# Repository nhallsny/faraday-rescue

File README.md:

# faraday-rescue
Open source battery for e-bikes made by the now-defunct Faraday Bicycles

This respository contains designs for an e-bike battery which replaces the original battery in Faraday e-bikes (utilizing exactly nothing from the original battery design!). This design fixes the major flaw in the original design, a high quiescent current which would quickly brick batteries if left un-tended.

## Repository

[build](https://github.com/nhallsny/faraday-rescue/tree/main/build) - CAD/Gerbers

- [cad](https://github.com/nhallsny/faraday-rescue/tree/main/build/cad) - files for printing, lasering, etc
	
- [pcb](https://github.com/nhallsny/faraday-rescue/tree/main/build/pcb) - Gerbers and Kicad project
	
- [build guide](https://github.com/nhallsny/faraday-rescue/tree/main/build/README.md) - Build Instructions
 
[reference](https://github.com/nhallsny/faraday-rescue/tree/main/reference) - design docs, build instructions, original documentation

- [design reference](https://github.com/nhallsny/faraday-rescue/tree/main/reference/design/README.md) - Design Doc
	
- [official](https://github.com/nhallsny/faraday-rescue/tree/main/reference/official) - Original docs and software tools from Faraday
	
- [rebuild](https://github.com/nhallsny/faraday-rescue/tree/main/reference/rebuild) - Instructions to only replace cells
 
[software](https://github.com/nhallsny/faraday-rescue/tree/main/software) - Code
- [bms software](https://github.com/nhallsny/faraday-rescue/tree/main/main/software/bms) - microcontroller code

[test](https://github.com/nhallsny/faraday-rescue/tree/main/test) - How to verify BMS function
- [realtime](https://github.com/nhallsny/faraday-rescue/tree/main/main/test/realtime) - datalogging templates and results

My revived Faraday:

## Battery Redesign Overview

Like the original design, this battery is a 12S 2P 18650 based design. It utilize a PCB the length of the battery for both 'high current' (10A) bussing and for the major BMS controls. Given that the original batteries were designed in 2013, batteries made with modern (2025 as of writing this) have roughly 20% more energy, boosting the range of the bike. However, that's not why this project exists...the project exists because of the many sad Faraday bikes and their unhappy owners. 

Why are their bikes sad? The original battery design has a quiescent draw of around 10mW even when 'off'. While it might not sound like much, that tiny amount of power will drain batteries from 0% state of charge to "bricked" i.e. copper dendrite formation in 2-3 weeks. Left unplugged over the winter, or even a long vacation, the batteries would be irreperably harmed.

How does this battery fix the sleep problem? Modern technology! When the bike was designed, there were no quiescent-optimized battery monitoring chips on the market that could measure 12 cells. The original designer chose an LTC6802-G...a good choice at the time, but designed for electric vehicle batteries with oodles of amp-hours. It doesn't help that the microcontroller on the BMS never seems to sleep. By using a low-power processor, sleep states, and a TI BQ 16-cell BMS chip, I was able to achieve:
+ Original design, off: 300uA
+ This design, off: 3uA

This means that when off, the improved battery can be left at 0% state-of-charge for roughly 5 years before it's a useless hunk of lithium, copper, and cobalt!

### Hardware
+ 12S 2P divided into 8 'modules'
+ Titanium or Fiberglass tube (you choose!)
+ TI BQ76972 fully integrated battery monitoring chip
+ STM32L0 Low-power microprocessor

+ RS485 driver

_Detailed hardware build files are in the [build]([url](https://github.com/nhallsny/faraday-rescue/tree/main/build)) folder

### Software
+ BQ chip implements overvoltage, undervoltage, balancing, temp measurement, high-side FET control, all the super important stuff
+ STM32 manages communications (required!) with the rest of the bike over RS485 and sleep/wake states
+ Currently implemented in C using the STM32 HAL

_Software, debug tools, etc are in the [software](https://github.com/nhallsny/faraday-rescue/tree/main/softwareac) folder_

LICENSE

README.md

## Build instructions
[Build instructions & BOM](https://github.com/nhallsny/faraday-rescue/tree/main/build/README.md)
[JLCPCB BOM](https://github.com/nhallsny/faraday-rescue/blob/main/build/pcb/faraday-rescue-bms/jlcpcb/production_files/BOM-pcb_battery.csv)
Test instructions --> TODO

## Goals

Beautiful, complex objects of the 21st century require 21st techniques to keep them running. Car restoration has been around as long as there have cars, bicycles are no different. However, unlike classic bicycles, e-bikes tend to become e-waste at the first sign of trouble, especially if the company isn't around to provide parts or documentation. In putting this info out there, I hope:
+ Bicycle companies will consider putting documentation for designs online before shutting off part supply forever
+ Motivated enthusiasts (like myself) will consider taking the plunge to keep machines they value alive for another few years.

## Team

+ Project initiator: Nathan Hall-Snyder @nhallsny
+ Contributors:
	+ _[transistor-man](https://github.com/transistor-man) [check out his build log here!](https://transistor-man.com/faraday_bike_revival.html)_

## License

This project is released under CERN Open Hardware Licence Version 2 - Permissive
You can modify and reuse as you like.

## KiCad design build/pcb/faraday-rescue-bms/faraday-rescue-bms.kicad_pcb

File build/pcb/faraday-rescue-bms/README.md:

# faraday-rescue/build/pcb/faraday-rescue-bms

PCB attached to battery modules that measures voltages, protects battery, manages sleep/wake, communicates with Faraday bike over RS485

## Revision table
### Release 2.1
- Change RS485 TVS diodes to bidirectional

### Release 2.0	
  - Fixed incorrect diode footprints
  - Fixed C15 Silk
  - Added VSS Test Point
  - Adjust I2C Pullups to 1.5kOhms
  - Add Cell0-VSS GND tie
  - Add more bulk capacitance near STM32 and RS485 Chip
  - Increase capacitance on BUTTON for more debouncing
  - Change shunt for a smaller one
  - Add thermal reliefs for SMT components on ground planes
  - Remove CHG and DSG test points
  - Add easy test points for sleep current measurement
  - Change thermistor capacitance to <470pF
  - Change to larger 20A slow-blow fuse for higher voltage rating
  - Add picoblade connector for RS485/button connector
  - Changing programming header to picoblade

Considered but not implemented:
  - Add bluetooth module for STM32
  - Switch Linear regulator to switching regulator
### 1.0
Initial Release

## Using these files
These files were designed in KiCad 8.0.4. There are two PCBs to fit in JLCPCB's design rules:
- Long, thin pcb which contains the BQ chip, STM32, and connectors
- Small stub board to complete the 8th module.

### Manufacturing parameters
If sending out this PCB, I suggest the following for the main PCB:
- 1mm board thickness (to fit inside tube)
- 2oz copper thickness on all layers (to reduce resistive heating. May not be necessary at 9A max current)
- Higher Tg material to avoid degredation of insulation during operation

For the smaller stub PCB:
- 1mm board thickness
- 1oz copper
- Higher Tg material to avoid degradation of insulation during operation

Ordering parameters from JLCPCB:

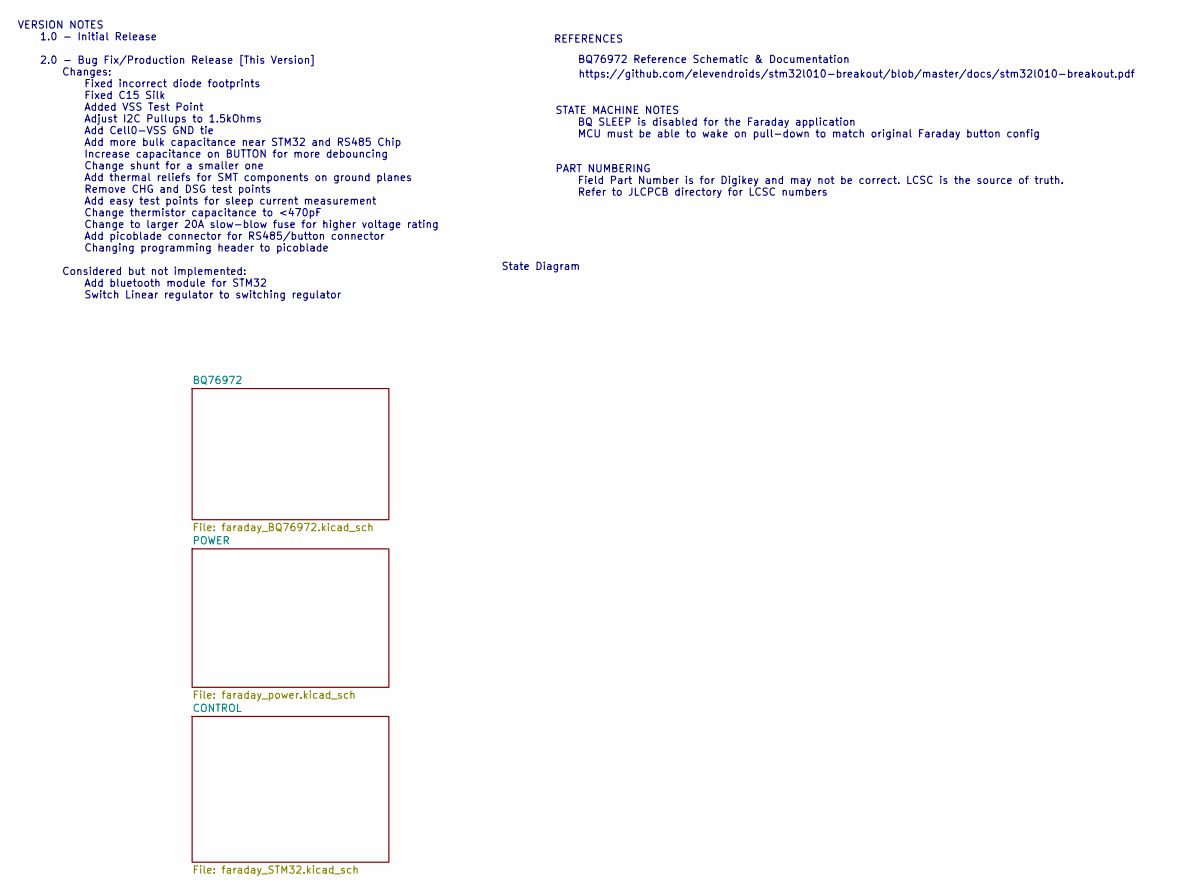
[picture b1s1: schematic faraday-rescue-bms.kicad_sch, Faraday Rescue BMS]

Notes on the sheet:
https://github.com/elevendroids/stm32l010-breakout/blob/master/docs/stm32l010-breakout.pdf
REFERENCES
BQ76972 Reference Schematic & Documentation
VERSION NOTES 1.0 - Initial Release 2.0 - Bug Fix/Production Release [This Version] Changes: Fixed incorrect diode footprints Fixed C15 Silk Added VSS Test Point Adjust I2C Pullups to 1.5kOhms Add Cell0-VSS GND tie Add more bulk capacitance near STM32 and RS485 Chip Increase capacitance on BUTTON f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
State Diagram
STATE MACHINE NOTES BQ SLEEP is disabled for the Faraday application MCU must be able to wake on pull-down to match original Faraday button config
PART NUMBERING Field Part Number is for Digikey and may not be correct. LCSC is the source of truth. Refer to JLCPCB directory for LCSC numbers

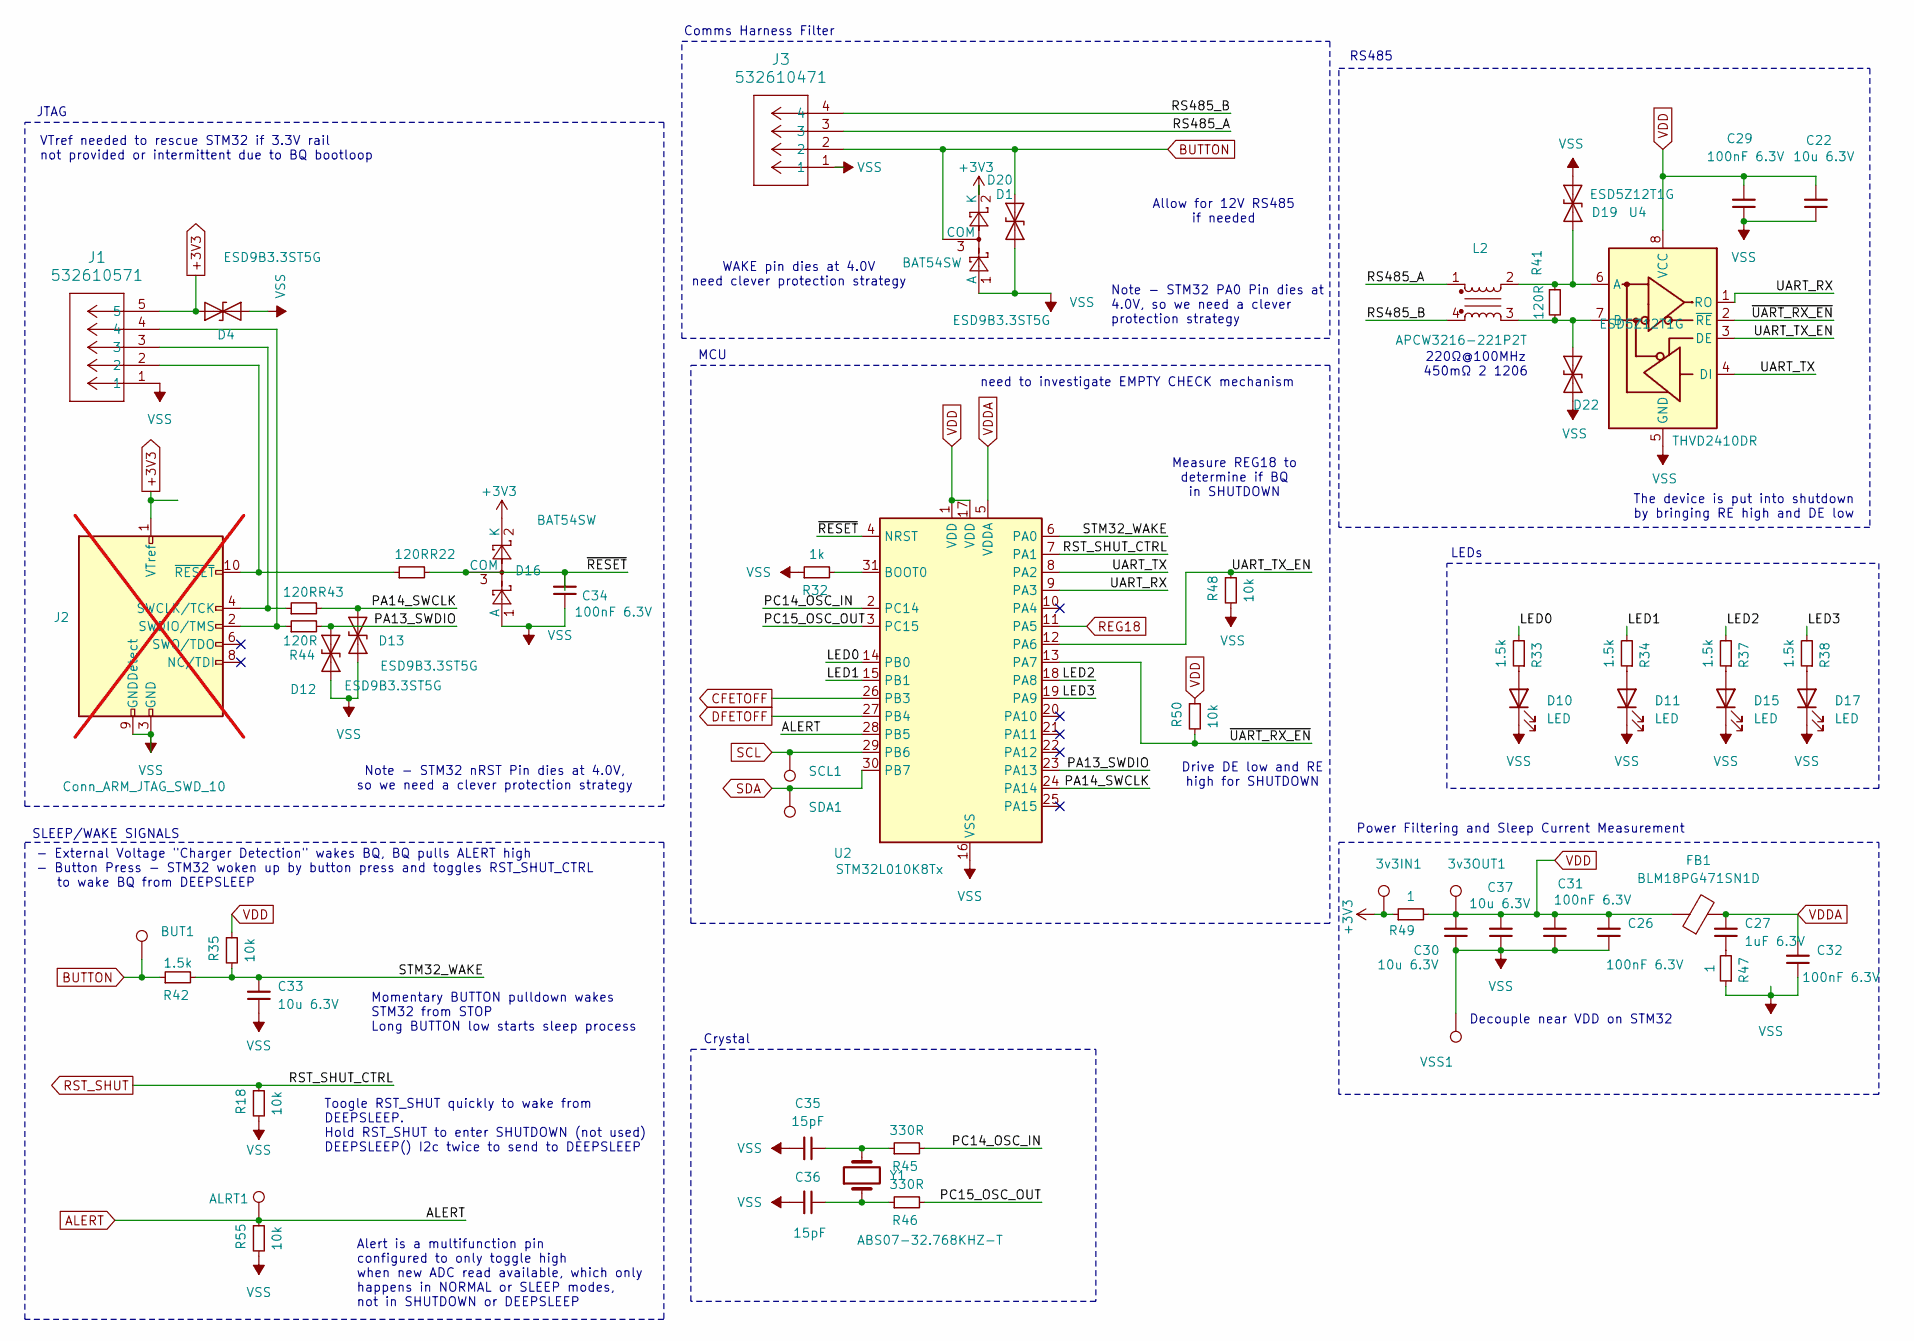
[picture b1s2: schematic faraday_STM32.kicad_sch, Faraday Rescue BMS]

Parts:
3v3IN1, 3v3OUT1: TestPoint_Keystone_5019_Minature; Part Number 36-5019CT-ND
ALRT1: TestPoint_Keystone_5019_Minature; Part Number 36-5019CT-ND
BUT1: TestPoint_Keystone_5019_Minature; Part Number 36-5019CT-ND
C22, C30, C37: 10u 6.3V; C_0402_1005Metric; Part Number CL05A106MP5NUNC
C26, C29, C31, C32, C34: 100nF 6.3V; C_0402_1005Metric; Part Number CC0402KRX7R7BB104
C27: 1uF 6.3V; C_0402_1005Metric; Part Number GRT155R61C105KE01D
C33: 10u 6.3V; C_0402_1005Metric; Part Number CC0402KRX7R7BB104
C35, C36: 15pF; C_0402_1005Metric; Part Number GJM1555C1H150GB01D
D1, D16: BAT54SW; SOT-323_SC-70; Part Number BAT54SW
D4, D12, D13, D20: ESD9B3.3ST5G; D_SOD-923; Part Number ESD9B3.3ST5G
D10, D11, D15, D17: LED; LED_0402_1005Metric; Part Number VLMO1500-GS08
D19, D22: ESD5Z12T1G; D_SOD-523; Part Number ESD5Z12T1G
FB1: BLM18PG471SN1D; L_0603_1608Metric; Part Number BLM18PG471SN1D
J1: 532610571; CONN_532610001-SD_05_MOL
J2: Conn_ARM_JTAG_SWD_10; PinHeader_2x05_P1.27mm_Vertical_SMD; Part Number 1156861; not fitted
J3: 532610471; CONN_532610001-SD_04_MOL
L2: APCW3216-221P2T; L_CommonMode_Wurth_WE-CNSW-1206; Part Number WCM3216F2SF-261T03
R18, R35, R48, R50, R55: 10k; R_0402_1005Metric; Part Number RC0402JR-0710KL
R22, R41, R43, R44: 120R; R_0402_1005Metric; Part Number RC0402JR-07120RL
R32: 1k; R_0402_1005Metric; Part Number RC0402JR-0710KL
R33, R34, R37, R38: 1.5k; R_0402_1005Metric; Part Number RC0402FR-07330RL
R42: 1.5k; R_0402_1005Metric; Part Number RC0402JR-07120RL
R45, R46: 330R; R_0402_1005Metric; Part Number RC1005J000CS
R47: 1; R_0402_1005Metric; Part Number RC0402JR-0710KL
R49: 1; R_0402_1005Metric; Part Number RC0402FR-071RL
SCL1: TestPoint_Keystone_5019_Minature; Part Number 36-5019CT-ND
SDA1: TestPoint_Keystone_5019_Minature; Part Number 36-5019CT-ND
U2: STM32L010K8Tx; LQFP-32_7x7mm_P0.8mm; Part Number STM32L010K8T6TR
U4: THVD2410DR; SOIC-8_3.9x4.9mm_P1.27mm; Part Number THVD2410DR
VSS1: TestPoint_Keystone_5019_Minature; Part Number 36-5019CT-ND
Y1: ABS07-32.768KHZ-T; R_1206_3216Metric; Part Number ABS07-32.768KHZ-T

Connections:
+3V3: 3v3IN1.1, D1.2 (K), D4.1 (A1), D16.2 (K), J1.5, J2.1 (VTref), R49.1; also elsewhere on the board
/CONTROL/LED0: R33.2, U2.14 (PB0)
/CONTROL/LED1: R34.2, U2.15 (PB1)
/CONTROL/LED2: R37.2, U2.18 (PA8)
/CONTROL/LED3: R38.2, U2.19 (PA9)
/CONTROL/PA13_SWDIO: D12.2 (A2), R44.2, U2.23 (PA13)
/CONTROL/PA14_SWCLK: D13.2 (A2), R43.2, U2.24 (PA14)
/CONTROL/PC14_OSC_IN: R45.2, U2.2 (PC14)
/CONTROL/PC15_OSC_OUT: R46.2, U2.3 (PC15)
/CONTROL/RS485_A: J3.3, L2.1
/CONTROL/RS485_B: J3.4, L2.4
/CONTROL/STM32_WAKE: C33.2, R35.2, R42.2, U2.6 (PA0)
/CONTROL/UART_RX: U2.9 (PA3), U4.1 (RO)
/CONTROL/UART_TX: U2.8 (PA2), U4.4 (DI)
/CONTROL/UART_TX_EN: R48.1, U2.12 (PA6), U4.3 (DE)
/CONTROL/~RESET: C34.2, D16.3 (COM), R22.2, U2.4 (NRST)
/CONTROL/~UART_RX_EN: R50.2, U2.13 (PA7), U4.2 (~RE)
ALERT: ALRT1.1, R55.1, U2.28 (PB5); also elsewhere on the board
BUTTON: BUT1.1, D1.3 (COM), D20.2 (A2), J3.2, R42.1
CFETOFF: U2.26 (PB3); also elsewhere on the board
DFETOFF: U2.27 (PB4); also elsewhere on the board
unnamed 37: J1.7, J3.6; also elsewhere on the board
unnamed: C27.1, R47.2
unnamed: C35.1, R45.1, Y1.2
unnamed: C36.1, R46.1, Y1.1
unnamed: D10.2 (A), R33.1
unnamed: D11.2 (A), R34.1
unnamed: D15.2 (A), R37.1
unnamed: D17.2 (A), R38.1
unnamed: D19.1 (A1), L2.2, R41.1, U4.6 (A)
unnamed: D22.1 (A1), L2.3, R41.2, U4.7 (B)
unnamed: J1.2, J2.10 (~RESET), R22.1
unnamed: J1.3, J2.4 (SWCLK/TCK), R43.1
unnamed: J1.4, J2.2 (SWDIO/TMS), R44.1
unnamed: R32.2, U2.31 (BOOT0)
REG18: U2.11 (PA5); also elsewhere on the board
RST_SHUT: R18.1, U2.7 (PA1); also elsewhere on the board
SCL: SCL1.1, U2.29 (PB6); also elsewhere on the board
SDA: SDA1.1, U2.30 (PB7); also elsewhere on the board
VDD: 3v3OUT1.1, C22.2, C26.2, C29.2, C30.2, C31.2, C37.2, FB1.1, R35.1, R49.2, R50.1, U2.1 (VDD), U2.17 (VDD), U4.8 (VCC)
VDDA: C27.2, C32.2, FB1.2, U2.5 (VDDA)
VSS: C22.1, C26.1, C29.1, C30.1, C31.1, C32.1, C33.1, C34.1, C35.2, C36.2, C37.1, D1.1 (A), D4.2 (A2), D10.1 (K), D11.1 (K), D12.1 (A1), D13.1 (A1), D15.1 (K), D16.1 (A), D17.1 (K), D19.2 (A2), D20.1 (A1), D22.2 (A2), J1.1, J1.6, J2.3 (GND), J2.5 (GND), J2.9 (GNDDetect), J3.1, J3.5, R18.2, R32.1, R47.1, R48.2, R55.2, U2.16 (VSS), U2.32 (VSS), U4.5 (GND), VSS1.1; also elsewhere on the board

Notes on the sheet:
220Ω@100MHz 450mΩ 2 1206
Decouple near VDD on STM32
Alert is a multifunction pin configured to only toggle high when new ADC read available, which only happens in NORMAL or SLEEP modes, not in SHUTDOWN or DEEPSLEEP
MCU
Note - STM32 PA0 Pin dies at 4.0V, so we need a clever protection strategy
RS485
WAKE pin dies at 4.0V need clever protection strategy
JTAG
Drive DE low and RE high for SHUTDOWN
- External Voltage "Charger Detection" wakes BQ, BQ pulls ALERT high - Button Press - STM32 woken up by button press and toggles RST_SHUT_CTRL to wake BQ from DEEPSLEEP
VTref needed to rescue STM32 if 3.3V rail not provided or intermittent due to BQ bootloop
Allow for 12V RS485 if needed
Momentary BUTTON pulldown wakes STM32 from STOP Long BUTTON low starts sleep process
SLEEP/WAKE SIGNALS
need to investigate EMPTY CHECK mechanism
Power Filtering and Sleep Current Measurement
Comms Harness Filter
Measure REG18 to determine if BQ in SHUTDOWN
The device is put into shutdown by bringing RE high and DE low
Toogle RST_SHUT quickly to wake from DEEPSLEEP. Hold RST_SHUT to enter SHUTDOWN (not used) DEEPSLEEP() I2c twice to send to DEEPSLEEP
Crystal
Note - STM32 nRST Pin dies at 4.0V, so we need a clever protection strategy
LEDs

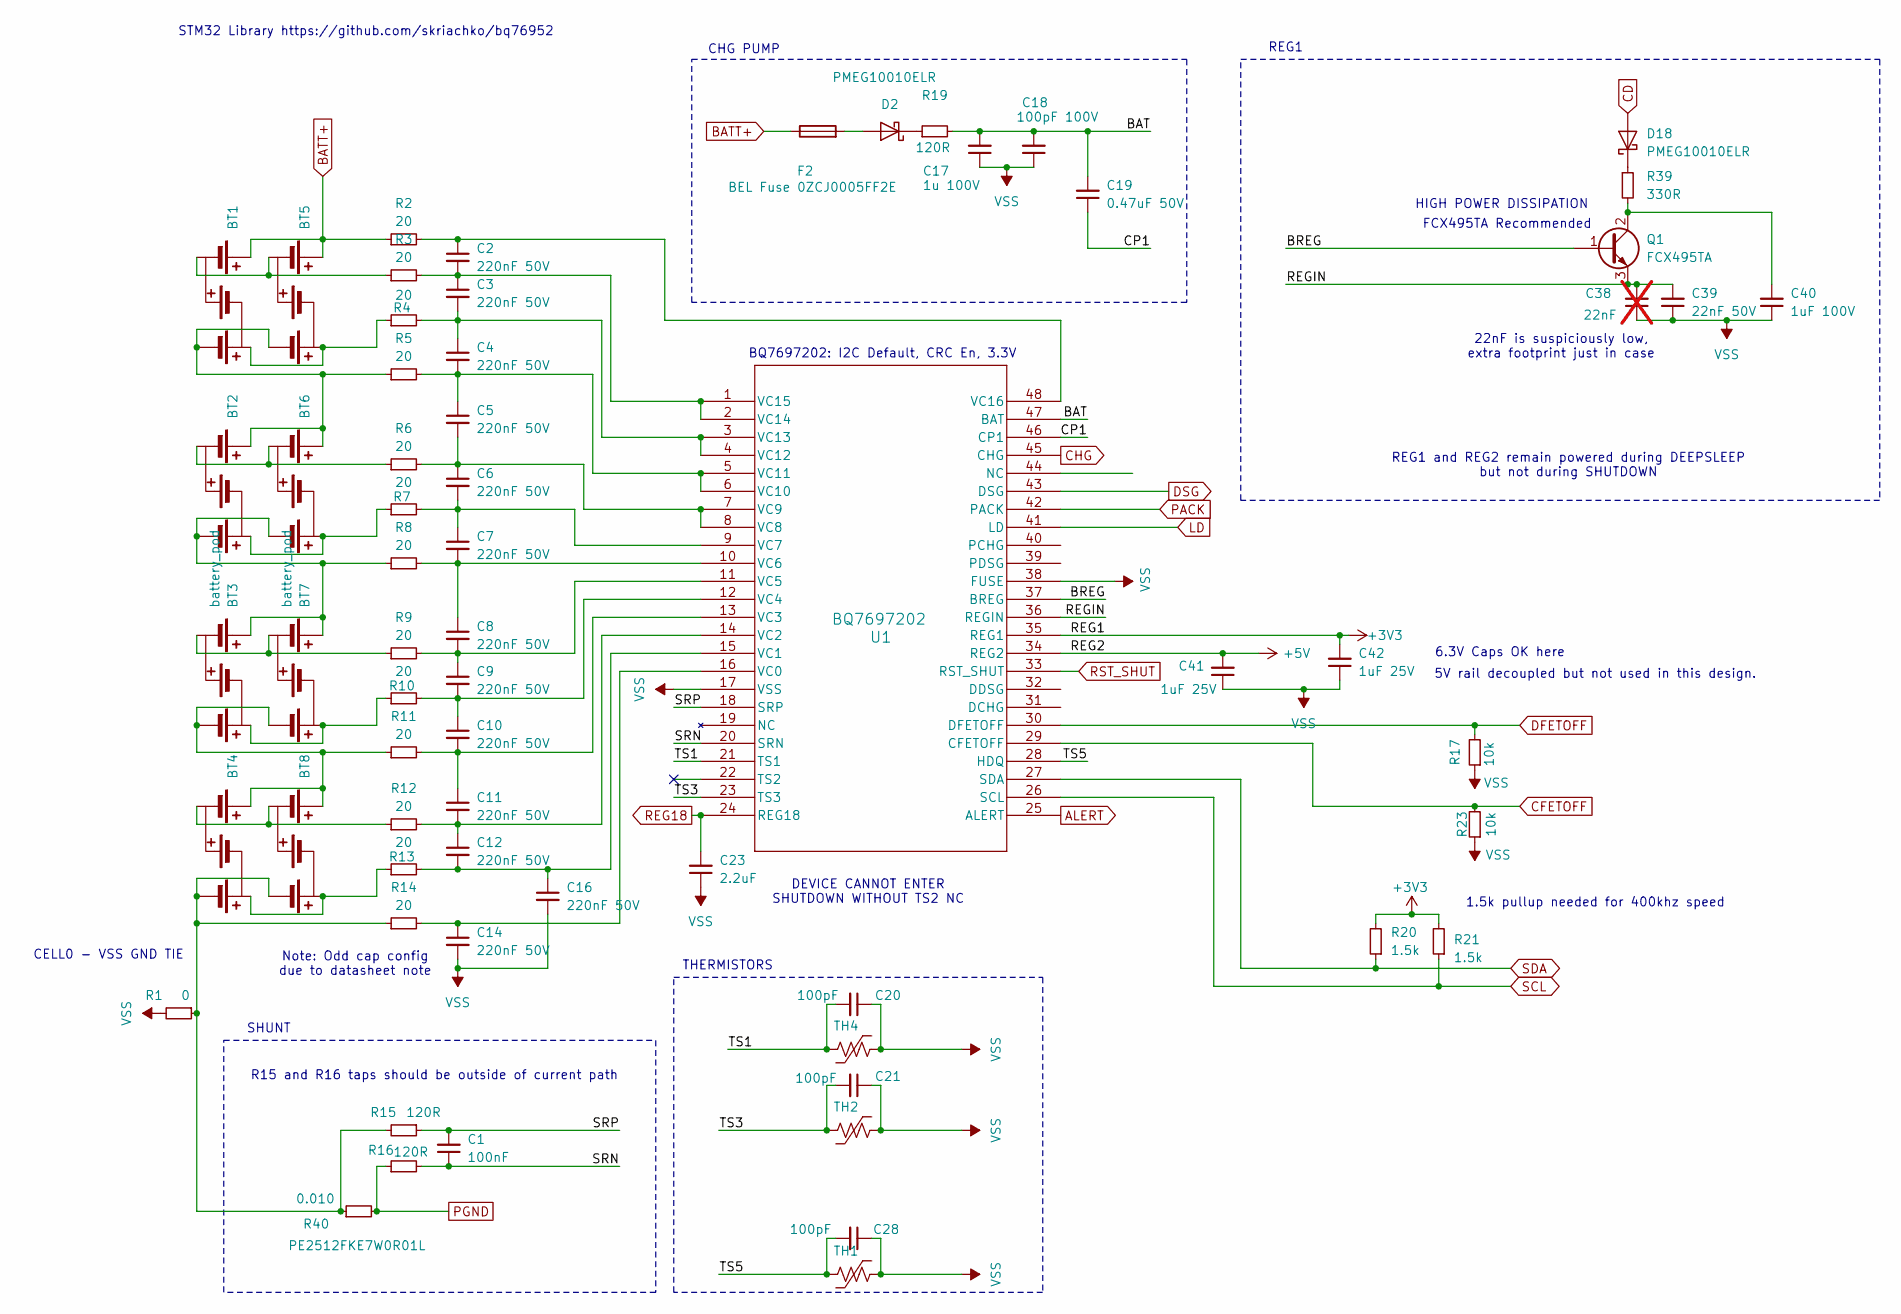
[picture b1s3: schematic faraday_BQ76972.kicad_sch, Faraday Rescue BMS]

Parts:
BT1, BT2, BT3, BT4, BT5, BT6, BT7, BT8: battery_pod; 3S 18650 Group
C1: 100nF; C_0402_1005Metric; Part Number CC0402KRX7R7BB104
C2, C3, C4, C5, C6, C7, C8, C9, C10, C11, C12, C14, C16: 220nF 50V; C_0402_1005Metric; Part Number GRM155R61H224KE01W
C17: 1u 100V; C_0805_2012Metric; Part Number CL21Y105KCYVPNE
C18: 100pF 100V; C_0805_2012Metric; Part Number CL21C101JC61PNC
C19: 0.47uF 50V; C_0805_2012Metric; Part Number CC0805KKX7R0BB474
C20, C21, C28: 100pF; C_0402_1005Metric; Part Number CC0402KRX7R7BB104
C23: 2.2uF; C_0402_1005Metric; Part Number CC0402KRX5R7BB225
C38: 22nF; C_0402_1005Metric; Part Number GRM155R71H223KA12D; not fitted
C39: 22nF 50V; C_0402_1005Metric; Part Number GRM155R71H223KA12D
C40: 1uF 100V; C_0805_2012Metric; Part Number CL21Y105KCYVPNE
C41, C42: 1uF 25V; C_0402_1005Metric; Part Number GRT155R61C105KE01D
D2, D18: PMEG10010ELR; Nexperia_CFP3_SOD-123W; Part Number PMEG10010ELR-QX
F2: BEL Fuse 0ZCJ0005FF2E; Fuse_1206_3216Metric; Part Number 0ZCJ0005FF2E
Q1: FCX495TA; SOT-89-3; Part Number FCX495TA
R1: 0; R_0402_1005Metric; Part Number RC0402JR-07120RL
R2, R3, R4, R5, R6, R7, R8, R9, R10, R11, R12, R13, R14: 20; R_1206_3216Metric; Part Number ESR18EZPF20R0
R15, R16: 120R; R_0402_1005Metric; Part Number RC0402JR-07120RL
R17, R23: 10k; R_0402_1005Metric; Part Number RC0402JR-0710KL
R19: 120R; R_1206_3216Metric; Part Number RC0402JR-07120RL
R20, R21: 1.5k; R_0402_1005Metric; Part Number RC0402JR-0710KL
R39: 330R; R_1206_3216Metric; Part Number RC0402FR-07330RL
R40: 0.010; R_2512_6332Metric; Part Number PE2512FKE7W0R01L
TH1, TH2: Thermistor_US; R_0402_1005Metric; Part Number NT04104F3435B1F
TH4: Thermistor_US; R_0402_1005Metric; Part Number CMFX 103F3435
U1: BQ7697202; TQFP48_PFB_TEX; Part Number BQ7697202PFBR

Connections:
+3V3: C42.2, R20.2, R21.2, U1.35 (REG1); also elsewhere on the board
+5V: C41.2, U1.34 (REG2)
/BQ76972/BAT: C17.2, C18.2, C19.2, R19.2, U1.47 (BAT)
/BQ76972/BREG: Q1.1 (B), U1.37 (BREG)
/BQ76972/CP1: C19.1, U1.46 (CP1)
/BQ76972/REGIN: C38.2, C39.2, Q1.3 (E), U1.36 (REGIN)
/BQ76972/SRN: C1.1, R16.2, U1.20 (SRN)
/BQ76972/SRP: C1.2, R15.1, U1.18 (SRP)
/BQ76972/TS1: C20.2, TH4.1, U1.21 (TS1)
/BQ76972/TS3: C21.2, TH2.1, U1.23 (TS3)
/BQ76972/TS5: C28.2, TH1.1, U1.28 (HDQ)
ALERT: U1.25 (ALERT); also elsewhere on the board
BATT+: BT1.1 (+), BT5.1 (+), F2.1, R2.1; also elsewhere on the board
CD: D18.2 (A); also elsewhere on the board
CFETOFF: R23.2, U1.29 (CFETOFF); also elsewhere on the board
CHG: U1.45 (CHG); also elsewhere on the board
DFETOFF: R17.2, U1.30 (DFETOFF); also elsewhere on the board
DSG: U1.43 (DSG); also elsewhere on the board
LD: U1.41 (LD); also elsewhere on the board
unnamed 37: BT1.3 (+), BT5.3 (+), R4.1; also elsewhere on the board
unnamed: BT1.2 (-), BT5.2 (-), R3.1
unnamed: BT1.4 (-), BT2.1 (+), BT5.4 (-), BT6.1 (+), R5.1
unnamed: BT2.3 (+), BT6.3 (+), R7.1
unnamed: BT2.2 (-), BT6.2 (-), R6.1
unnamed: BT2.4 (-), BT3.1 (+), BT6.4 (-), BT7.1 (+), R8.1
unnamed: BT3.3 (+), BT7.3 (+), R10.1
unnamed: BT3.2 (-), BT7.2 (-), R9.1
unnamed: BT3.4 (-), BT4.1 (+), BT7.4 (-), BT8.1 (+), R11.1
unnamed: BT4.3 (+), BT8.3 (+), R13.1
unnamed: BT4.2 (-), BT8.2 (-), R12.1
unnamed: BT4.4 (-), BT8.4 (-), R1.1, R14.1, R15.2, R40.1
unnamed: D2.2 (A), F2.2
unnamed: D2.1 (K), R19.1
unnamed: D18.1 (K), R39.1
unnamed: C40.2, Q1.2 (C), R39.2
unnamed: C14.1, R14.2, U1.16 (VC0)
unnamed: C12.2, C16.1, R13.2, U1.15 (VC1)
unnamed: C11.2, C12.1, R12.2, U1.14 (VC2)
unnamed: C10.2, C11.1, R11.2, U1.13 (VC3)
unnamed: C9.2, C10.1, R10.2, U1.12 (VC4)
unnamed: C8.2, C9.1, R9.2, U1.11 (VC5)
unnamed: C7.2, C8.1, R8.2, U1.10 (VC6)
unnamed: C6.2, C7.1, R7.2, U1.9 (VC7)
unnamed: C5.2, C6.1, R6.2, U1.7 (VC9), U1.8 (VC8)
unnamed: C4.2, C5.1, R5.2, U1.5 (VC11), U1.6 (VC10)
unnamed: C3.2, C4.1, R4.2, U1.3 (VC13), U1.4 (VC12)
unnamed: C2.2, C3.1, R3.2, U1.1 (VC15), U1.2 (VC14)
unnamed: C2.1, R2.2, U1.48 (VC16)
PACK: U1.42 (PACK); also elsewhere on the board
PGND: R16.1, R40.2; also elsewhere on the board
REG18: C23.2, U1.24 (REG18); also elsewhere on the board
RST_SHUT: U1.33 (RST_SHUT); also elsewhere on the board
SCL: R21.1, U1.26 (SCL); also elsewhere on the board
SDA: R20.1, U1.27 (SDA); also elsewhere on the board
VSS: C14.2, C16.2, C17.1, C18.1, C20.1, C21.1, C23.1, C28.1, C38.1, C39.1, C40.1, C41.1, C42.1, R1.2, R17.1, R23.1, TH1.2, TH2.2, TH4.2, U1.17 (VSS), U1.38 (FUSE); also elsewhere on the board

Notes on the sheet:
BQ7697202: I2C Default, CRC En, 3.3V
CELL0 - VSS GND TIE
STM32 Library https://github.com/skriachko/bq76952
REG1
CHG PUMP
5V rail decoupled but not used in this design.
R15 and R16 taps should be outside of current path
Note: Odd cap config due to datasheet note
22nF is suspiciously low, extra footprint just in case
REG1 and REG2 remain powered during DEEPSLEEP but not during SHUTDOWN
THERMISTORS
SHUNT
DEVICE CANNOT ENTER SHUTDOWN WITHOUT TS2 NC
6.3V Caps OK here
1.5k pullup needed for 400khz speed
FCX495TA Recommended
HIGH POWER DISSIPATION

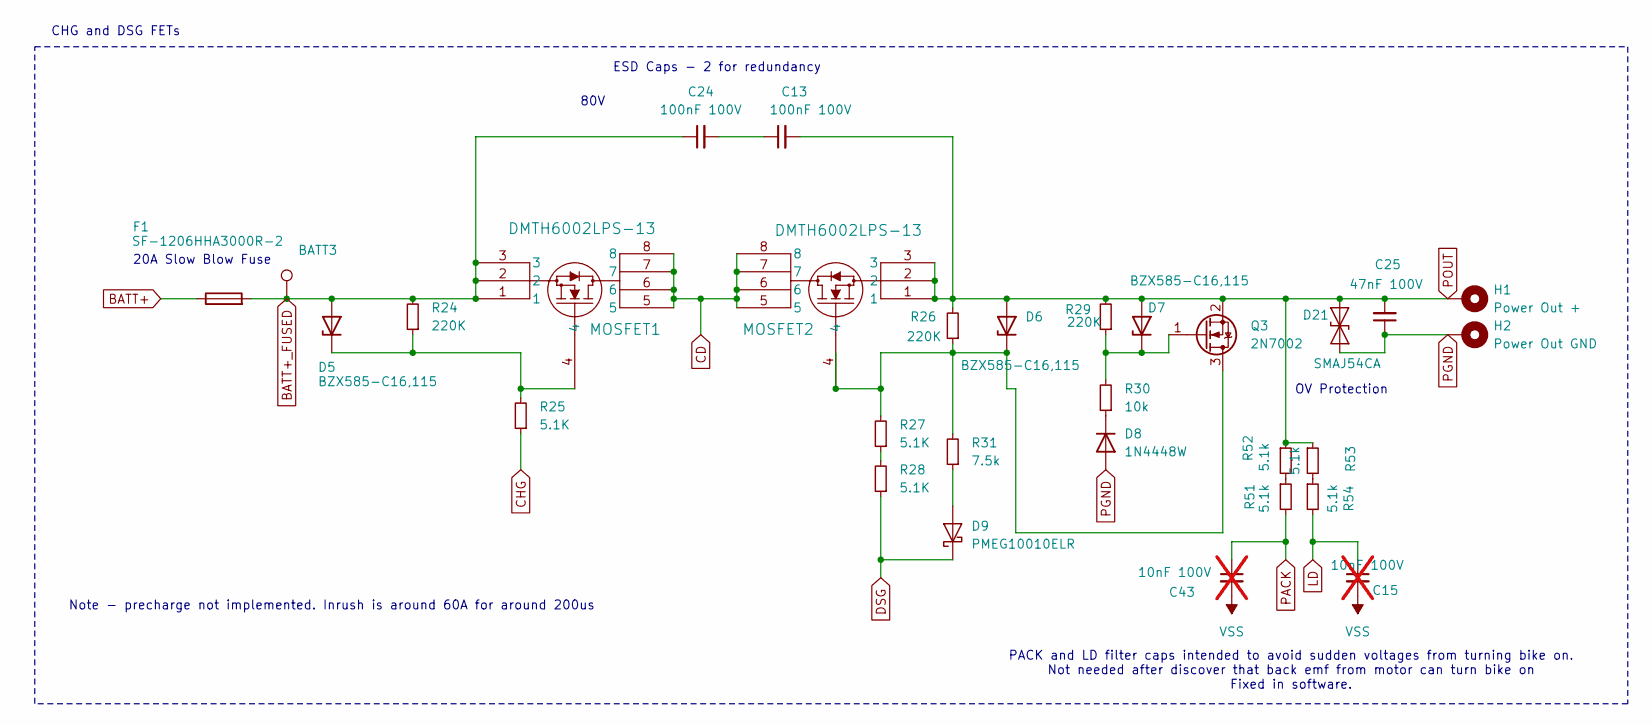
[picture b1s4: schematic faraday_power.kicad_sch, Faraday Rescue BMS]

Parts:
BATT3: TestPoint_Keystone_5019_Minature; Part Number 36-5019CT-ND
C13, C24: 100nF 100V; C_0603_1608Metric; Part Number CL10B104KC8NNNC
C15, C43: 10nF 100V; C_0805_2012Metric; Part Number CGA4J2X7R2A473K125AA; not fitted
C25: 47nF 100V; C_0805_2012Metric; Part Number CGA4J2X7R2A473K125AA
D5, D6, D7: BZX585-C16,115; D_SOD-523; Part Number BZX585-C16,115
D8: 1N4448W; D_SOD-123; Part Number 1N4448W
D9: PMEG10010ELR; Nexperia_CFP3_SOD-123W; Part Number PMEG10010ELR-QX
D21: SMAJ54CA; D_SMA; Part Number SMAJ54CA
F1: SF-1206HHA3000R-2; R_1206_3216Metric; Part Number SF-1206HHA3000R-2
H1: Power Out +; MountingHole_2.5mm_Pad_Via
H2: Power Out GND; MountingHole_2.5mm_Pad_Via
MOSFET1, MOSFET2: DMTH6002LPS-13; POWERDI5060-8_K_DIO; Part Number DMTH6002LPS-13
Q3: 2N7002; SOT-23; Part Number 2N7002
R24, R26, R29: 220K; R_0402_1005Metric; Part Number RC0402FR-07220KL
R25, R27, R28: 5.1K; R_0402_1005Metric; Part Number RC0402FR-075K1L
R30: 10k; R_0402_1005Metric; Part Number RC0402JR-0710KL
R31: 7.5k; R_0402_1005Metric; Part Number RC0402FR-077K5L
R51, R52, R53, R54: 5.1k; R_0402_1005Metric; Part Number RC0402FR-075K1L

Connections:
BATT+: F1.1; also elsewhere on the board
BATT+_FUSED: BATT3.1, C24.1, D5.2 (A), F1.2, MOSFET1.1, MOSFET1.2, MOSFET1.3, R24.2
CD: MOSFET1.5, MOSFET1.6, MOSFET1.7, MOSFET1.8, MOSFET2.5, MOSFET2.6, MOSFET2.7, MOSFET2.8; also elsewhere on the board
CHG: R25.1; also elsewhere on the board
DSG: D9.1 (K), R28.1; also elsewhere on the board
LD: C15.1, R54.2; also elsewhere on the board
unnamed: C13.1, C24.2
unnamed: D5.1 (K), MOSFET1.4, R24.1, R25.2
unnamed: D6.1 (K), MOSFET2.4, Q3.3 (D), R26.1, R27.2, R31.2
unnamed: D7.1 (K), Q3.1 (G), R29.1, R30.2
unnamed: D8.1 (K), R30.1
unnamed: D9.2 (A), R31.1
unnamed: R27.1, R28.2
unnamed: R51.1, R52.2
unnamed: R53.2, R54.1
PACK: C43.1, R51.2; also elsewhere on the board
PGND: C25.1, D8.2 (A), D21.1 (A1), H2.1; also elsewhere on the board
POUT: C13.2, C25.2, D6.2 (A), D7.2 (A), D21.2 (A2), H1.1, MOSFET2.1, MOSFET2.2, MOSFET2.3, Q3.2 (S), R26.2, R29.2, R52.1, R53.1
VSS: C15.2, C43.2; also elsewhere on the board

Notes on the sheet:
ESD Caps - 2 for redundancy
20A Slow Blow Fuse
Note - precharge not implemented. Inrush is around 60A for around 200us
OV Protection
CHG and DSG FETs
80V
PACK and LD filter caps intended to avoid sudden voltages from turning bike on. Not needed after discover that back emf from motor can turn bike on Fixed in software.

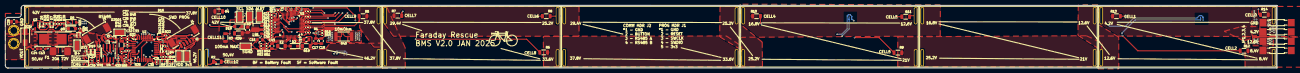
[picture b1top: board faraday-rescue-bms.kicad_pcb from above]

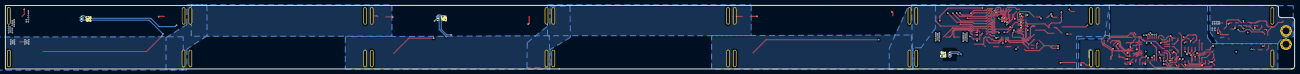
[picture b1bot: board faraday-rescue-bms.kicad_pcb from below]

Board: 4 copper layers, 481.3 x 23.7 mm, 151 parts (6 on the bottom side), 98 nets.

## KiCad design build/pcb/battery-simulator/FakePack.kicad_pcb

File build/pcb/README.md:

# faraday-rescue/build/pcb
Contains KICAD (produced in KiCAD 8.0.4 of the following:
- faraday-rescue-bms - the main thing, the schematic, layout, and manufacturing files for the PCB that turns a bunch of cells into a battery
- battery-simulator - simple PCB with 12 resistors in series for testing BMS functions such as overvoltage, undervoltage, leakage currents, etc

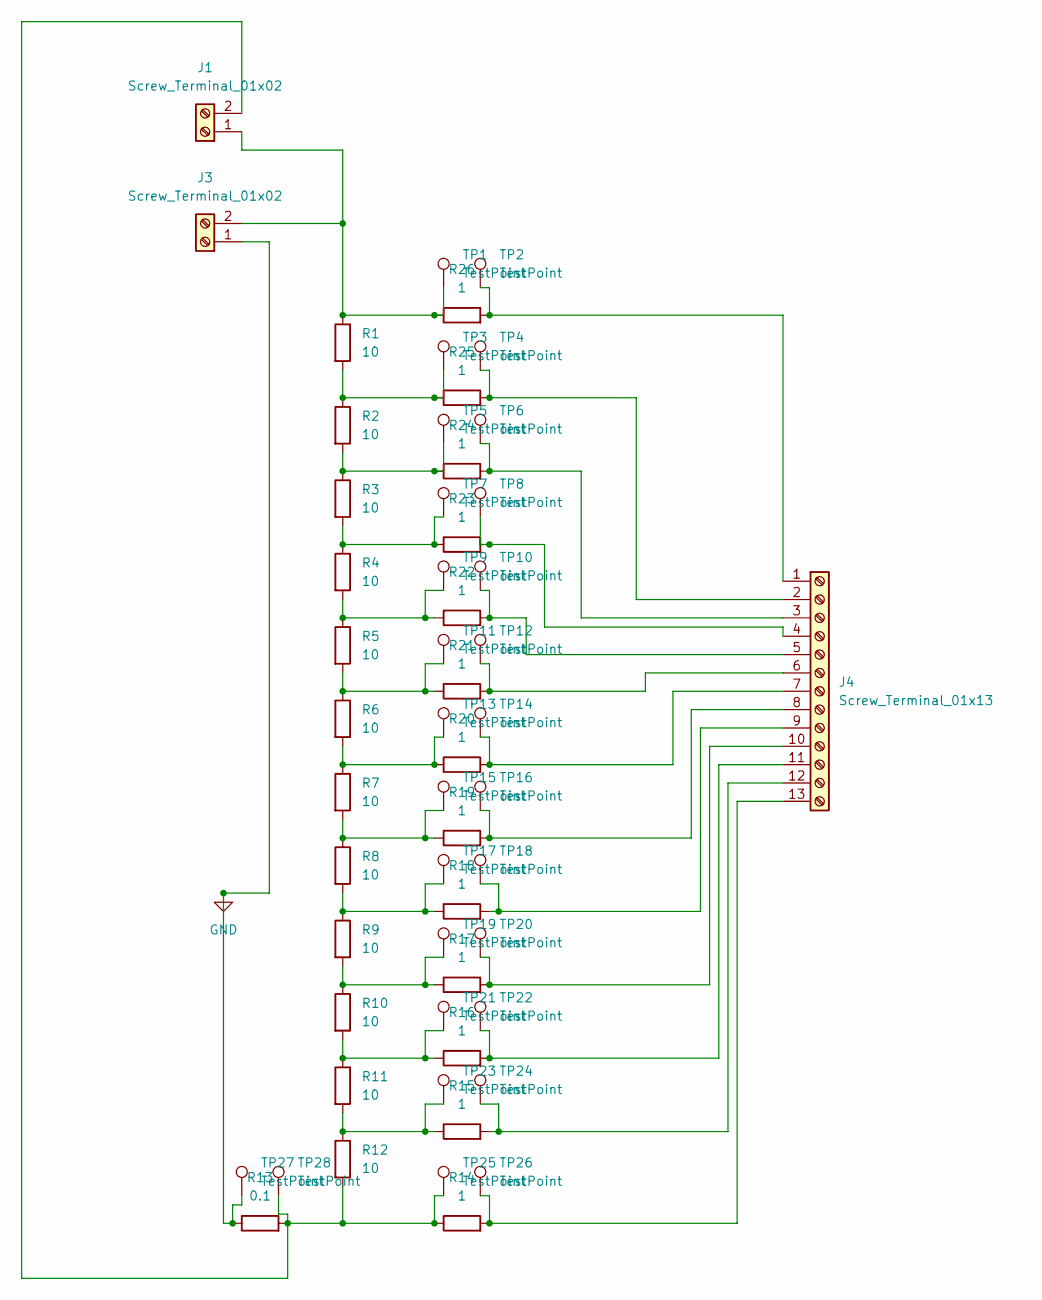
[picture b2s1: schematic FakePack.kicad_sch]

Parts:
J1, J3: Screw_Terminal_01x02; TerminalBlock_4Ucon_1x02_P3.50mm_Horizontal
J4: Screw_Terminal_01x13; TerminalBlock_Xinya_XY308-2.54-13P_1x13_P2.54mm_Horizontal
R1, R2, R3, R4, R5, R6, R7, R8, R9, R10, R11, R12: 10; R_Axial_DIN0918_L18.0mm_D9.0mm_P22.86mm_Horizontal
R13: 0.1; R_1206_3216Metric
R14, R15, R16, R17, R18, R19, R20, R21, R22, R23, R24, R25, R26: 1; R_0805_2012Metric
TP1, TP2, TP3, TP4, TP5, TP6, TP7, TP8, TP9, TP10, TP11, TP12, TP13, TP14, TP15, TP16, TP17, TP18, TP19, TP20, TP21, TP22, TP23, TP24, TP25, TP26, TP27, TP28: TestPoint; TestPoint_Keystone_5010-5014_Multipurpose

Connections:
GND: J3.1, R13.1, TP27.1; also elsewhere on the board
unnamed 1: J1.1, J3.2, R1.1, R26.1, TP1.1; also elsewhere on the board
unnamed: J4.1, R26.2, TP2.1
unnamed: J4.2, R25.2, TP4.1
unnamed: J4.3, R24.2, TP6.1
unnamed: J4.4, R23.2, TP8.1
unnamed: J4.5, R22.2, TP10.1
unnamed: J4.6, R21.2, TP12.1
unnamed: J4.7, R20.2, TP14.1
unnamed: J4.8, R19.2, TP16.1
unnamed: J4.9, R18.2, TP18.1
unnamed: J4.10, R17.2, TP20.1
unnamed: J4.11, R16.2, TP22.1
unnamed: J4.12, R15.2, TP24.1
unnamed: J4.13, R14.2, TP26.1
unnamed: R1.2, R2.1, R25.1, TP3.1
unnamed: R2.2, R3.1, R24.1, TP5.1
unnamed: R9.2, R10.1, R17.1, TP19.1
unnamed: R10.2, R11.1, R16.1, TP21.1
unnamed: R11.2, R12.1, R15.1, TP23.1
unnamed: J1.2, R12.2, R13.2, R14.1, TP25.1, TP28.1
unnamed: R8.2, R9.1, R18.1, TP17.1
unnamed: R7.2, R8.1, R19.1, TP15.1
unnamed: R6.2, R7.1, R20.1, TP13.1
unnamed: R5.2, R6.1, R21.1, TP11.1
unnamed: R4.2, R5.1, R22.1, TP9.1
unnamed: R3.2, R4.1, R23.1, TP7.1

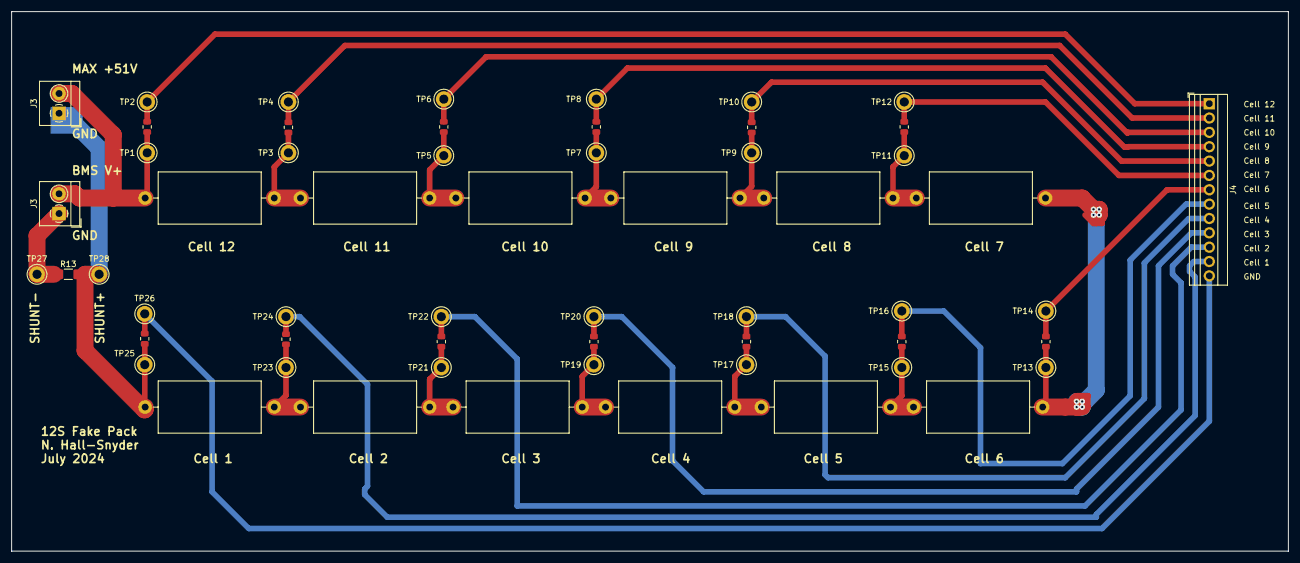
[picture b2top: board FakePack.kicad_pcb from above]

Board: 2 copper layers, 226.0 x 95.5 mm, 57 parts (0 on the bottom side), 27 nets.

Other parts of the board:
J3#2: Screw_Terminal_01x02; TerminalBlock_4Ucon_1x02_P3.50mm_Horizontal

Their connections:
GND: J3#2.1; also elsewhere on the board
unnamed 1: J3#2.2; also elsewhere on the board

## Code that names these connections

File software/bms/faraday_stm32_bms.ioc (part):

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Mcu.Name=STM32L010K8Tx
Mcu.Package=LQFP32
Mcu.UserName=STM32L010K8Tx
PA0.Mode=SYS_WakeUp0
PA0.Signal=SYS_WKUP1
PA1.Signal=GPIO_Output
PA13.Mode=Serial_Wire
PA13.Signal=SYS_SWDIO
PA14.Mode=Serial_Wire
PA14.Signal=SYS_SWCLK
PA2.Mode=Asynchronous
PA2.Signal=USART2_TX
PA3.Mode=Asynchronous
PA3.Signal=USART2_RX
PA5.Signal=SharedAnalog_PA5
PA8.Signal=GPIO_Output
PA9.Signal=GPIO_Output
PB0.Signal=GPIO_Output
PB1.Signal=GPIO_Output
PB3.Signal=GPIO_Output
PB4.Signal=GPIO_Output
PB5.Signal=GPIO_Input
PB6.Mode=I2C
PB6.Signal=I2C1_SCL
PB7.Mode=I2C
PB7.Signal=I2C1_SDA
PC14-OSC32_IN.Mode=LSE-External-Oscillator
PC14-OSC32_IN.Signal=RCC_OSC32_IN
PC15-OSC32_OUT.Mode=LSE-External-Oscillator
PC15-OSC32_OUT.Signal=RCC_OSC32_OUT
RCC.SYSCLKFreq_VALUE=4194000
board=custom

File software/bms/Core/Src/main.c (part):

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#define LED_DSG_PIN GPIO_PIN_1

//Active-high to veto charge FET
#define CFETOFF_PORT GPIOB
#define CFETOFF_PIN GPIO_PIN_3

//Active-high to veto discharge FET
#define DFETOFF_PORT GPIOB
#define DFETOFF_PIN GPIO_PIN_4

//Active-low on-button from faraday bike. Used in this file and stm32l0xx_it.c
#define BUTTON_PORT GPIOA
#define BUTTON_PIN GPIO_PIN_0

//RST_SHUT_CTRL used by STM to change BQ sleep states
#define RST_SHUT_PORT GPIOA
#define RST_SHUT_PIN GPIO_PIN_1

//REG18 analog value from BQ chip. Read to check if BQ is in SHUTDOWN
#define REG18_AIN_PORT GPIOA
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#define LED_SF_PIN GPIO_PIN_9

//Alert configurable output from BQ chip. Not used in this file, set in stm32l0xx_it.c
#define ALERT_PORT GPIOB
#define ALERT_PIN GPIO_PIN_5

//UART_TX_EN - enable transmit on RS485 transceiver, active high
#define UART_TX_EN_PORT GPIOA
#define UART_TX_EN_PIN GPIO_PIN_6

//UART_RX_EN - enable receive on RS485 transceiver, active low
#define UART_RX_EN_PORT GPIOA
#define UART_RX_EN_PIN GPIO_PIN_7

/*BQ Chip Parameters*/
#define ACTIVE_CELLS 0xAAFF //bitfield which indicates which cells to have protections on. Specific to this Faraday 12S pack
#define BQ_DEV_ADDR  0x10 //i2c address
#define BQ_CRC_MODE 1  // 0 for disabled, 1 for enabled

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}

void THVD2410_Sleep() {
	HAL_GPIO_WritePin(UART_TX_EN_PORT, UART_TX_EN_PIN, GPIO_PIN_RESET);
	HAL_GPIO_WritePin(UART_RX_EN_PORT, UART_RX_EN_PIN, GPIO_PIN_SET);
}
;
void THVD2410_Transmit() {
	HAL_GPIO_WritePin(UART_TX_EN_PORT, UART_TX_EN_PIN, GPIO_PIN_SET);
	HAL_GPIO_WritePin(UART_RX_EN_PORT, UART_RX_EN_PIN, GPIO_PIN_SET);
}
;
void THVD2410_Receive() {
	HAL_GPIO_WritePin(UART_TX_EN_PORT, UART_TX_EN_PIN, GPIO_PIN_RESET);
	HAL_GPIO_WritePin(UART_RX_EN_PORT, UART_RX_EN_PIN, GPIO_PIN_RESET);
}
;

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}

/* STM32_Stop - puts the STM32 into STOP mode at minimum power consumption.
 * Leaves two ways to wake - EXTI0_1 (PA0 pulldown) and EXTI2_3 (PB5 pullup)
 *
 * Note that this function will fail if IWDG is running. This must be called before IWDG is started to be successful*/
void STM32_Stop() {
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	//Turn off RS485 Chip
	THVD2410_Sleep();

	//Configure wake Interrupt on ALERT pin
	EXTI2_3_IRQHandler_Config();

	//Configure wake interrupt on BUTTON pin
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/* Update FET LEDs with most recent status */
void STM32_UpdateFETLEDs() {

	HAL_GPIO_WritePin(LED_CHG_PORT, LED_CHG_PIN, batt.Chg);
	HAL_GPIO_WritePin(LED_DSG_PORT, LED_DSG_PIN, batt.Dsg);
}

/**
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	}

	/* Initialize BQ State*/
	BQ769x2_ResetShutdownPin(&batt); // RST_SHUT pin set low just in case
	BQ769x2_InitState(&batt, &hi2c1, BQ_DEV_ADDR, BQ_CRC_MODE, &htim2,
	ACTIVE_CELLS, RST_SHUT_PORT, RST_SHUT_PIN, CFETOFF_PORT, CFETOFF_PIN,
	DFETOFF_PORT, DFETOFF_PIN);

	delayMS(&htim2, 50); //Wait for everything to stabilize

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PUTCHAR_PROTOTYPE {
	/* Place your implementation of fputc here */
	/* e.g. write a character to the EVAL_COM1 and Loop until the end of transmission */
	HAL_GPIO_WritePin(UART_RX_EN_PORT, UART_RX_EN_PIN, GPIO_PIN_SET); // Receive Off
	delayUS(&htim2, 20);
	HAL_GPIO_WritePin(UART_TX_EN_PORT, UART_TX_EN_PIN, GPIO_PIN_SET); // Transmit On
	delayUS(&htim2, 20);
	HAL_UART_Transmit(&huart2, (uint8_t*) &ch, 1, 0xFFFF);
	HAL_GPIO_WritePin(UART_TX_EN_PORT, UART_TX_EN_PIN, GPIO_PIN_RESET); //Transmit off
	delayUS(&htim2, 20);
	HAL_GPIO_WritePin(UART_RX_EN_PORT, UART_RX_EN_PIN, GPIO_PIN_SET); // Receive still off
	delayUS(&htim2, 20);

	return ch;
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	HAL_GPIO_WritePin(GPIOB,
	GPIO_PIN_0 | GPIO_PIN_1 | GPIO_PIN_3 | GPIO_PIN_4, GPIO_PIN_RESET);

	/*Configure GPIO pins : PA1 PA8 PA9 */
	GPIO_InitStruct.Pin = GPIO_PIN_1 | GPIO_PIN_6 | GPIO_PIN_7 | GPIO_PIN_8
			| GPIO_PIN_9;
	GPIO_InitStruct.Mode = GPIO_MODE_OUTPUT_PP;
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	GPIO_InitStruct.Speed = GPIO_SPEED_FREQ_LOW;
	HAL_GPIO_Init(GPIOA, &GPIO_InitStruct);

	/*Configure GPIO pins : PB0 PB1 PB3 PB4 */
	GPIO_InitStruct.Pin = GPIO_PIN_0 | GPIO_PIN_1 | GPIO_PIN_3 | GPIO_PIN_4;
	GPIO_InitStruct.Mode = GPIO_MODE_OUTPUT_PP;
	GPIO_InitStruct.Pull = GPIO_NOPULL;
	GPIO_InitStruct.Speed = GPIO_SPEED_FREQ_LOW;
	HAL_GPIO_Init(GPIOB, &GPIO_InitStruct);

	/*Configure GPIO pin : PB5 */
	GPIO_InitStruct.Pin = GPIO_PIN_5;
	GPIO_InitStruct.Mode = GPIO_MODE_INPUT;
	GPIO_InitStruct.Pull = GPIO_NOPULL;
	HAL_GPIO_Init(GPIOB, &GPIO_InitStruct);

	/*Configure GPIO pin : PA0 */
	GPIO_InitStruct.Pin = GPIO_PIN_0;
	GPIO_InitStruct.Mode = GPIO_MODE_INPUT;
	GPIO_InitStruct.Pull = GPIO_PULLUP;
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

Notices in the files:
software/bms/Core/Src/main.c:
All rights reserved.
This software is licensed under terms that can be found in the LICENSE file
